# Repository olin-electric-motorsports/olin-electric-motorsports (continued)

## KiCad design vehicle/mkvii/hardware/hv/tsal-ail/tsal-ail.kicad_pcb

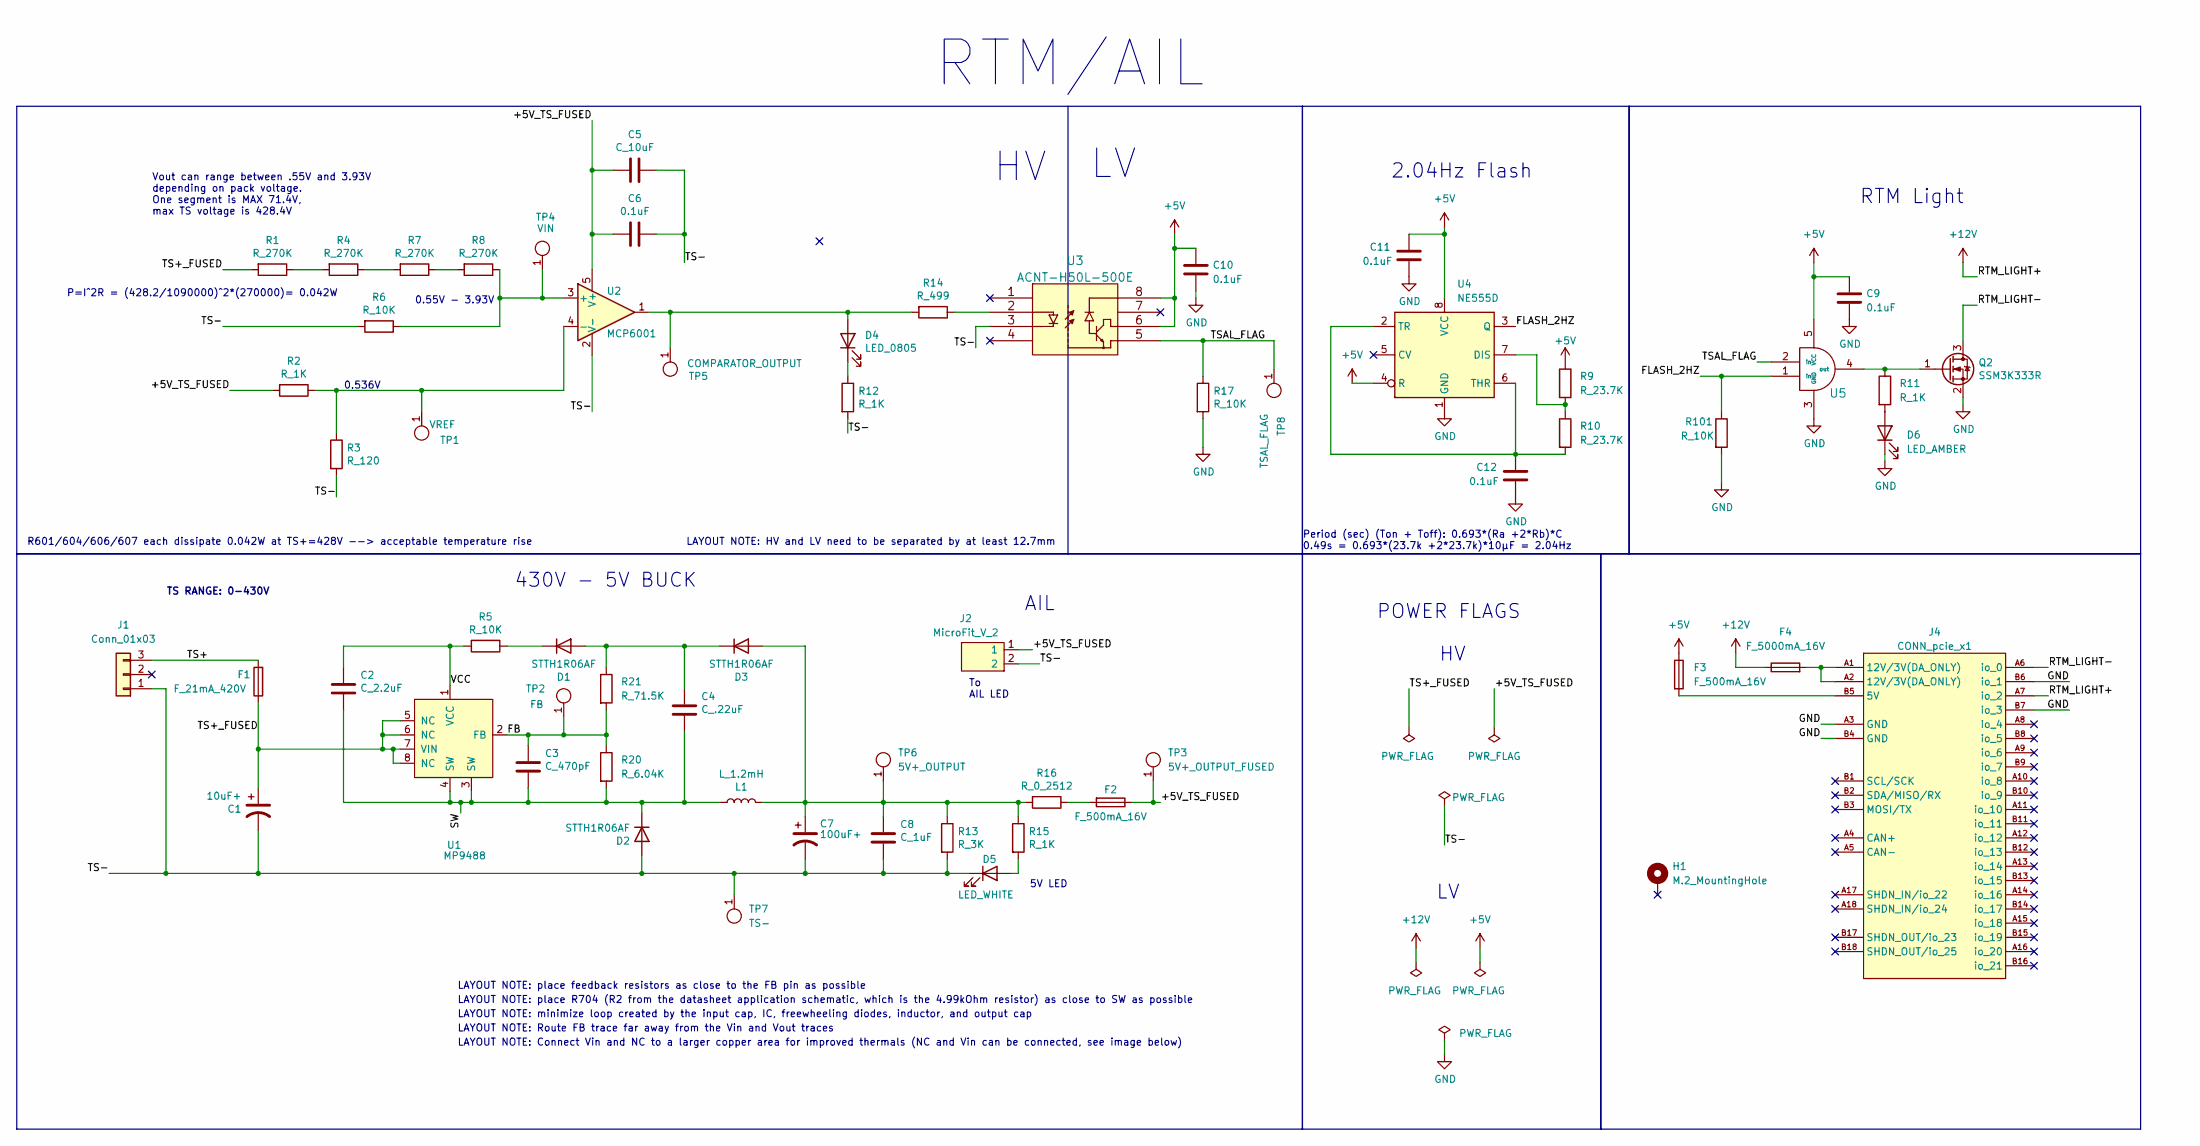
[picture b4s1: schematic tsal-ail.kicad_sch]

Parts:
C1: 10uF+; CP_Radial_D10.0mm_P5.00mm; MPN 450BXC10MEFC10X20
C2: C_2.2uF; C_0603; MPN GRM188R61E225KA12J
C3: C_470pF; C_0603; MPN 0603B471K500CT
C4: C_.22uF; C_0603; MPN CL10A224KB8NNNC
C5: C_10uF; C_0603; MPN LMK107BBJ106KALT
C6, C9, C10, C11, C12: 0.1uF; C_0603; MPN CL10B104KB8NNWC
C7: 100uF+; CP_Radial_D8.0mm_P3.50mm; MPN ESK107M050AG3EA
C8: C_1uF; C_0603; MPN CL10B105KA8NNNC
D1, D2, D3: STTH1R06AF; D_SOD-128; MPN STTH1R06AF
D4: LED_0805; CHIPLED_0805; MPN LTST-C170KFKT
D5: LED_WHITE; CHIPLED_0805; MPN B1701TW--20P000314U1930
D6: LED_AMBER; CHIPLED_0805
F1: F_21mA_420V; MPN B59884C0120A054
F2, F3: F_500mA_16V; Fuse_1210; MPN 0ZCH0050FF2G
F4: F_5000mA_16V; Fuse_1210; MPN 0ZCH0050FF2G
H1: M.2_MountingHole; M.2_Mount
J1: Conn_01x03; Molex_Micro-Fit_3.0_43650-0315_1x03_P3.00mm_Vertical
J2: MicroFit_V_2; MPN 0430450212
J4: CONN_pcie_x1; pcie_x1
L1: L_1.2mH; MPN RCP1317NP-122L
Q2: SSM3K333R; SOT-23F; MPN SSM3K333R,LF
R1, R4, R7, R8: R_270K; R_0603; MPN RMCF0603FT270K
R2, R11, R12, R15: R_1K; R_0603; MPN RMCF0603FT1K00
R3: R_120; R_0603; MPN RC0603FR-13120RL
R5, R6, R17, R101: R_10K; R_0603; MPN RMCF0603FT10K0
R9, R10: R_23.7K; R_0603; MPN RMCF0603FT22K0
R13: R_3K; R_0603; MPN RC0603FR-103KL
R14: R_499; R_0603; MPN RC0603FR-10499RL
R16: R_0_2512; R_2512_6332Metric; MPN CR2512-J/-000ELF
R20: R_6.04K; R_0603; MPN RMCF0603FT6K04
R21: R_71.5K; R_0603; MPN RMCF0603FT71K5
TP1: VREF; Test_Point_SMD; MPN 5019
TP2: FB; Test_Point_SMD; MPN 5019
TP3: 5V+_OUTPUT_FUSED; Test_Point_SMD; MPN 5019
TP4: VIN; Test_Point_SMD; MPN 5019
TP5: COMPARATOR_OUTPUT; Test_Point_SMD; MPN 5019
TP6: 5V+_OUTPUT; Test_Point_SMD; MPN 5019
TP7: TS-; Test_Point_SMD; MPN 5019
TP8: TSAL_FLAG; Test_Point_SMD; MPN 5019
U1: MP9488; Converter_DCDC_MPS_MP9488; MPN MP9488GS-Z
U2: MCP6001; SOT-353_SC-70-5; MPN MCP6001T-I/OT
U3: ACNT-H50L-500E; MPN ACNT-H50L-000E
U4: NE555D; SOIC-8_3.9x4.9mm_P1.27mm
U5: U_GATE_SN74LVC1G08DBVR; SOT-23-5_OEM; MPN SN74LVC1G08DBVR

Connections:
+5V: C9.1, C10.1, C11.2, F3.1, R9.1, U3.6, U3.8, U4.4 (R), U4.8 (VCC), U5.5 (VCC)
+12V: F4.1, J4.A7 (io_2)
/+5V_TS_FUSED: C5.2, C6.2, F2.1, J2.1, R2.2, TP3.1, U2.5 (V+)
/FB: C3.1, R20.1, R21.2, TP2.1, U1.2 (FB)
/FLASH_2HZ: R101.1, U4.3 (Q), U5.1 (in)
/RTM_LIGHT-: J4.A6 (io_0), Q2.3 (D)
/SW: C2.2, C3.2, C4.2, D2.1 (K), L1.1, R20.2, U1.3 (SW), U1.4 (SW)
/TS+: F1.2, J1.3
/TS+_FUSED: C1.1, F1.1, R1.2, U1.5 (NC), U1.6 (NC), U1.7 (VIN), U1.8 (NC)
/TS-: C1.2, C5.1, C6.1, C7.2, C8.2, D2.2 (A), D5.1 (K), J1.1, J2.2, R3.2, R6.2, R12.2, R13.2, TP7.1, U2.2 (V-), U3.3
/TSAL_FLAG: R17.1, TP8.1, U3.5, U5.2 (in)
/VCC: C2.1, R5.2, U1.1 (VCC)
GND: C9.2, C10.2, C11.1, C12.1, D6.1 (K), J4.A3 (GND), J4.B4 (GND), J4.B6 (io_1), J4.B7 (io_3), Q2.2 (S), R17.2, R101.2, U4.1 (GND), U5.3 (GND)
unnamed: C4.1, D1.2 (A), D3.1 (K), R21.1
unnamed: D1.1 (K), R5.1
unnamed: C7.1, C8.1, D3.2 (A), L1.2, R13.1, R15.1, R16.2, TP6.1
unnamed: D4.2 (A), R14.2, TP5.1, U2.1
unnamed: D4.1 (K), R12.1
unnamed: D5.2 (A), R15.2
unnamed: D6.2 (A), R11.2
unnamed: F2.2, R16.1
unnamed: F4.2, J4.A1 (12V/3V(DA_ONLY)), J4.A2 (12V/3V(DA_ONLY))
unnamed: F3.2, J4.B5 (5V)
unnamed: Q2.1 (G), R11.1, U5.4 (out)
unnamed: R1.1, R4.2
unnamed: R4.1, R7.2
unnamed: R7.1, R8.2
unnamed: R14.1, U3.2
unnamed: R6.1, R8.1, TP4.1, U2.3 (+)
unnamed: R2.1, R3.1, TP1.1, U2.4 (-)
unnamed: R9.2, R10.1, U4.7 (DIS)
unnamed: C12.2, R10.2, U4.2 (TR), U4.6 (THR)

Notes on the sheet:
LAYOUT NOTE: Route FB trace far away from the Vin and Vout traces
Period (sec) (Ton + Toff): 0.693*(Ra +2*Rb)*C 0.49s = 0.693*(23.7k +2*23.7k)*10µF = 2.04Hz
AIL
LAYOUT NOTE: minimize loop created by the input cap, IC, freewheeling diodes, inductor, and output cap
RTM Light
LAYOUT NOTE: Connect Vin and NC to a larger copper area for improved thermals (NC and Vin can be connected, see image below)
RTM/AIL
2.04Hz Flash
P=I^2R = (428.2/1090000)^2*(270000)= 0.042W
LAYOUT NOTE: place feedback resistors as close to the FB pin as possible
Vout can range between .55V and 3.93V depending on pack voltage. One segment is MAX 71.4V, max TS voltage is 428.4V
LAYOUT NOTE: place R704 (R2 from the datasheet application schematic, which is the 4.99kOhm resistor) as close to SW as possible
LAYOUT NOTE: HV and LV need to be separated by at least 12.7mm
5V LED
POWER FLAGS
0.536V
R601/604/606/607 each dissipate 0.042W at TS+=428V --> acceptable temperature rise
0.55V - 3.93V
TS RANGE: 0-430V
To AIL LED
430V - 5V BUCK

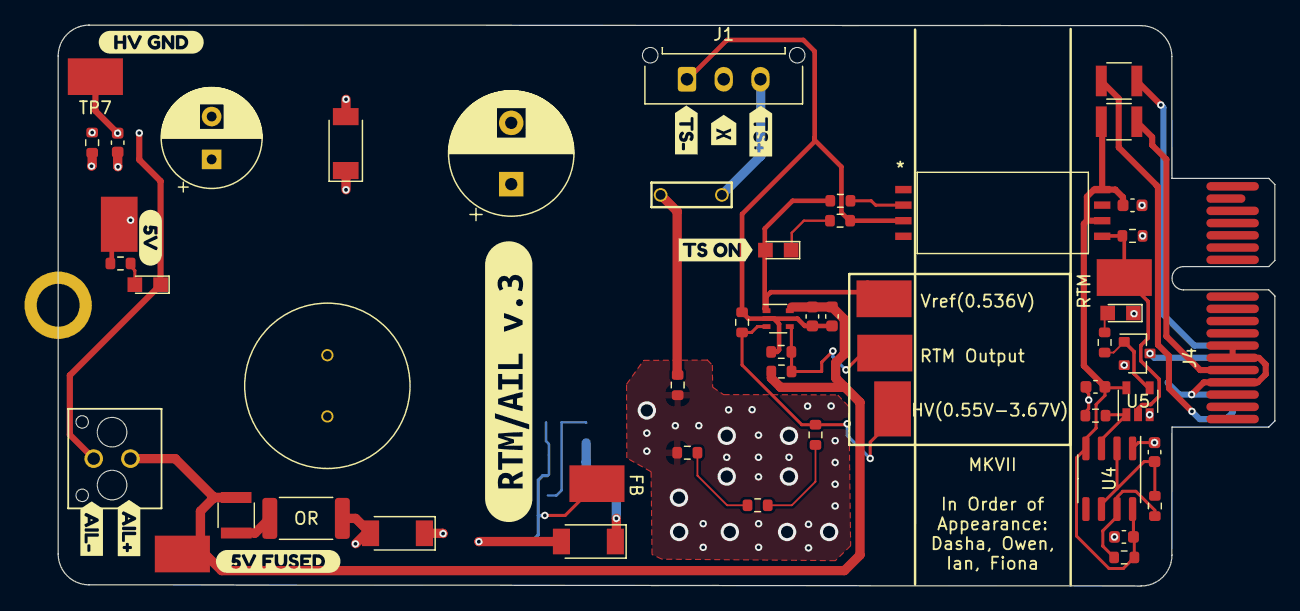
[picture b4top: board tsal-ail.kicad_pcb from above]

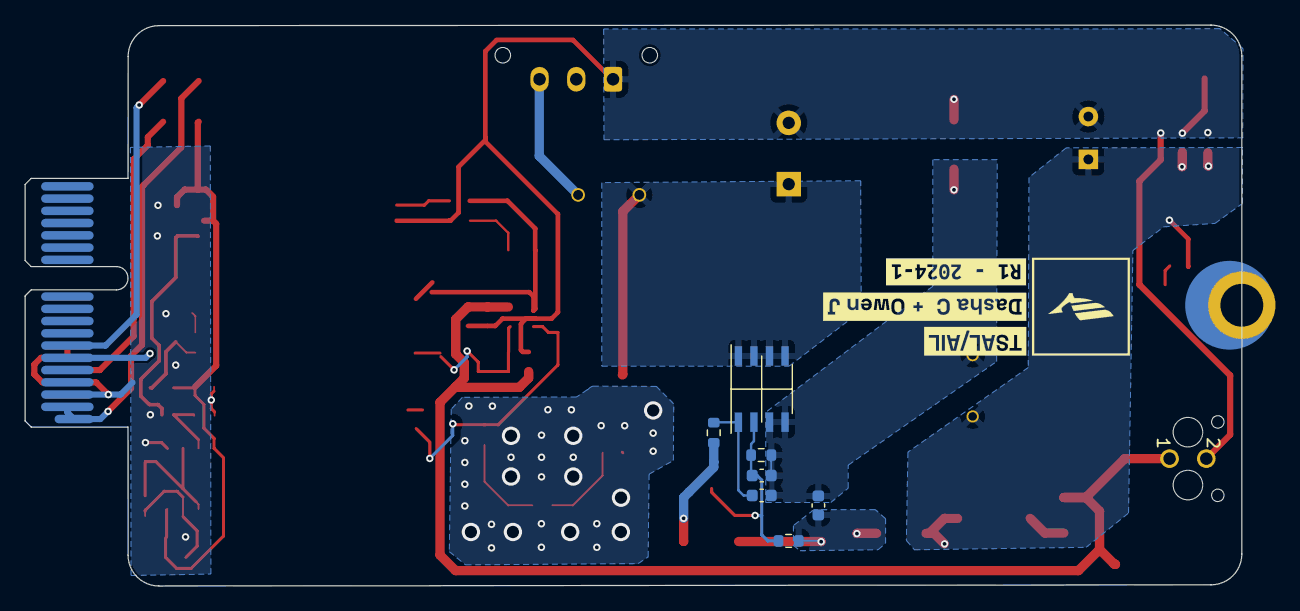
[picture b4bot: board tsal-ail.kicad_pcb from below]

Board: 2 copper layers, 99.3 x 45.8 mm, 74 parts (10 on the bottom side), 32 nets.

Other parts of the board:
kibuzzard-63AC91FD: G***; kibuzzard-63AC91FD
kibuzzard-63AC93EB: G***; kibuzzard-63AC93EB
kibuzzard-63AC93FC: G***; kibuzzard-63AC93FC
kibuzzard-63AC9220: G***; kibuzzard-63AC9220
kibuzzard-63AC9283: G***; kibuzzard-63AC9283
kibuzzard-63AC9446: G***; kibuzzard-63AC9446
kibuzzard-63AC9456: G***; kibuzzard-63AC9456
kibuzzard-63AD0077: G***; kibuzzard-63AD0077
kibuzzard-63D843BA: G***; kibuzzard-63D843BA
kibuzzard-63D84460: G***; kibuzzard-63D84460
kibuzzard-673C33E6: G***; kibuzzard-673C33E6
kibuzzard-6784A725: G***; kibuzzard-6784A725
kibuzzard-6784B342: G***; kibuzzard-6784B342

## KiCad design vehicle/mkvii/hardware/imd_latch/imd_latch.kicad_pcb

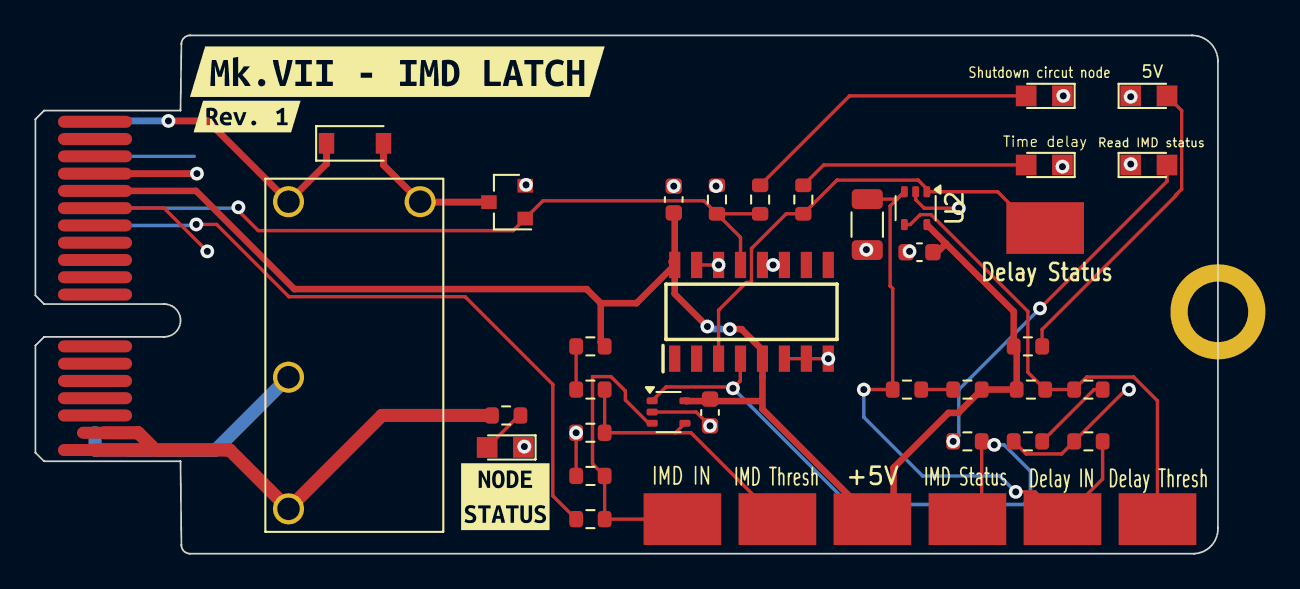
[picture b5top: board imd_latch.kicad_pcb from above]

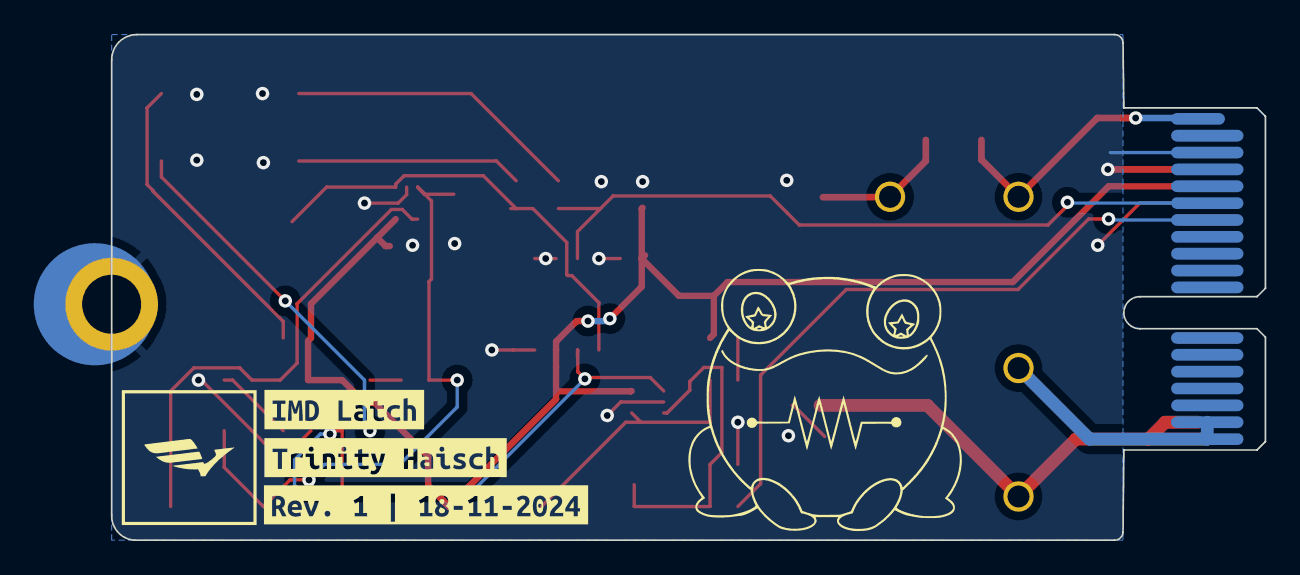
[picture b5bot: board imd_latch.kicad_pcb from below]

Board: 2 copper layers, 68.4 x 30.0 mm, 47 parts (3 on the bottom side), 22 nets.

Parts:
+5V: Test_Point_SMD
C1: C_22uF; C_1206_3216Metric
C2, C3, C4: 0.1uF; C_0603
D1: D_Schottky_SS110LW; D_SOD-123
D2, D4, D5: LED_AMBER; CHIPLED_0805
D3: LED_WHITE; CHIPLED_0805
D6: LED_BLUE; CHIPLED_0805
Delay IN: Test_Point_SMD
Delay Status: Test_Point_SMD
Delay Thresh: Test_Point_SMD
H1: M.2_MountingHole; M.2_Mount
IC1: CD4044BDR; SOIC127P600X175-16N
IMD IN: Test_Point_SMD
IMD Status: Test_Point_SMD
IMD Thresh: Test_Point_SMD
J2: CONN_pcie_x1; pcie_x1
K1: G5Q-1A4-DC12; Relay_SPST_OMRON-G5Q-1A4_OEM
Q1: SSM3K333R; SOT-23F
R1, R3, R4, R6, R7, R11: R_100K; R_0603
R2: R_71.5k; R_0603
R5: R_120K; R_0603
R8: R_3K; R_0603
R9, R13, R15, R16, R17: R_1K; R_0603
R10: R_1.82M; R_0603
R12: R_604K; R_0603
R14: R_330; R_0603
U1, U2: MCP6001; SOT-353_SC-70-5
kibuzzard-673ACD76: G***; kibuzzard-673ACD76
kibuzzard-673AD5BE: G***; kibuzzard-673AD5BE
kibuzzard-673AD5DE: G***; kibuzzard-673AD5DE
kibuzzard-673AD216: G***; kibuzzard-673AD216
kibuzzard-673AD632: G***; kibuzzard-673AD632
kibuzzard-673AE0C6: G***; kibuzzard-673AE0C6

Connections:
+5V: +5V.1, C2.1, C3.1, C4.1, IC1.5 (ENABLE), IC1.16 (VDD), J2.B5 (5V), R1.1, R2.2, R3.1, R14.2, U1.5 (V+), U2.5 (V+)
+BATT: D1.1 (K), J2.A1 (12V/3V(DA_ONLY)), K1.1
/IMD_OUTPUT: J2.A7 (io_2), R8.1
/IMD_STATUS: IC1.13 (Q1), J2.A6 (io_0), Q1.1 (G), R12.1, R13.1
/IMD_STATUS_OUTPUT: IC1.4 (RI), IMD Status.1, R15.1, U1.1
/SHDN_IN: J2.A17 (SHDN_IN/io_22), J2.A18 (SHDN_IN/io_24), K1.2
/SHDN_OUT: J2.B17 (SHDN_OUT/io_23), J2.B18 (SHDN_OUT/io_25), K1.3, R17.1
/TIME_DELAY: Delay Status.1, IC1.3 (SI), R16.1, U2.1
GND: C1.2, C2.2, C3.2, C4.2, D2.1 (K), D3.1 (K), D4.1 (K), D5.1 (K), D6.1 (K), H1.1, IC1.6 (R2), IC1.7 (S2), IC1.8 (VSS), IC1.11 (S3), IC1.12 (R3), IC1.14 (R4), IC1.15 (S4), J2.A3 (GND), J2.B4 (GND), J2.B6 (io_1), Q1.2 (S), R6.1, R7.1, R9.2, R10.2, R12.2, U1.2 (V-), U2.2 (V-)
unnamed: D1.2 (A), K1.5, Q1.3 (D)
unnamed: D2.2 (A), R15.2
unnamed: D3.2 (A), R14.1
unnamed: D4.2 (A), R13.2
unnamed: D5.2 (A), R16.2
unnamed: D6.2 (A), R17.2
unnamed: R2.1, R5.1
unnamed: R4.1, R7.2
unnamed: R3.2, R11.1
unnamed: IMD IN.1, R8.2, R9.1, U1.3 (+)
unnamed: IMD Thresh.1, R6.2, R11.2, U1.4 (-)
unnamed: C1.1, Delay IN.1, R5.2, R10.1, U2.3 (+)
unnamed: Delay Thresh.1, R1.2, R4.2, U2.4 (-)

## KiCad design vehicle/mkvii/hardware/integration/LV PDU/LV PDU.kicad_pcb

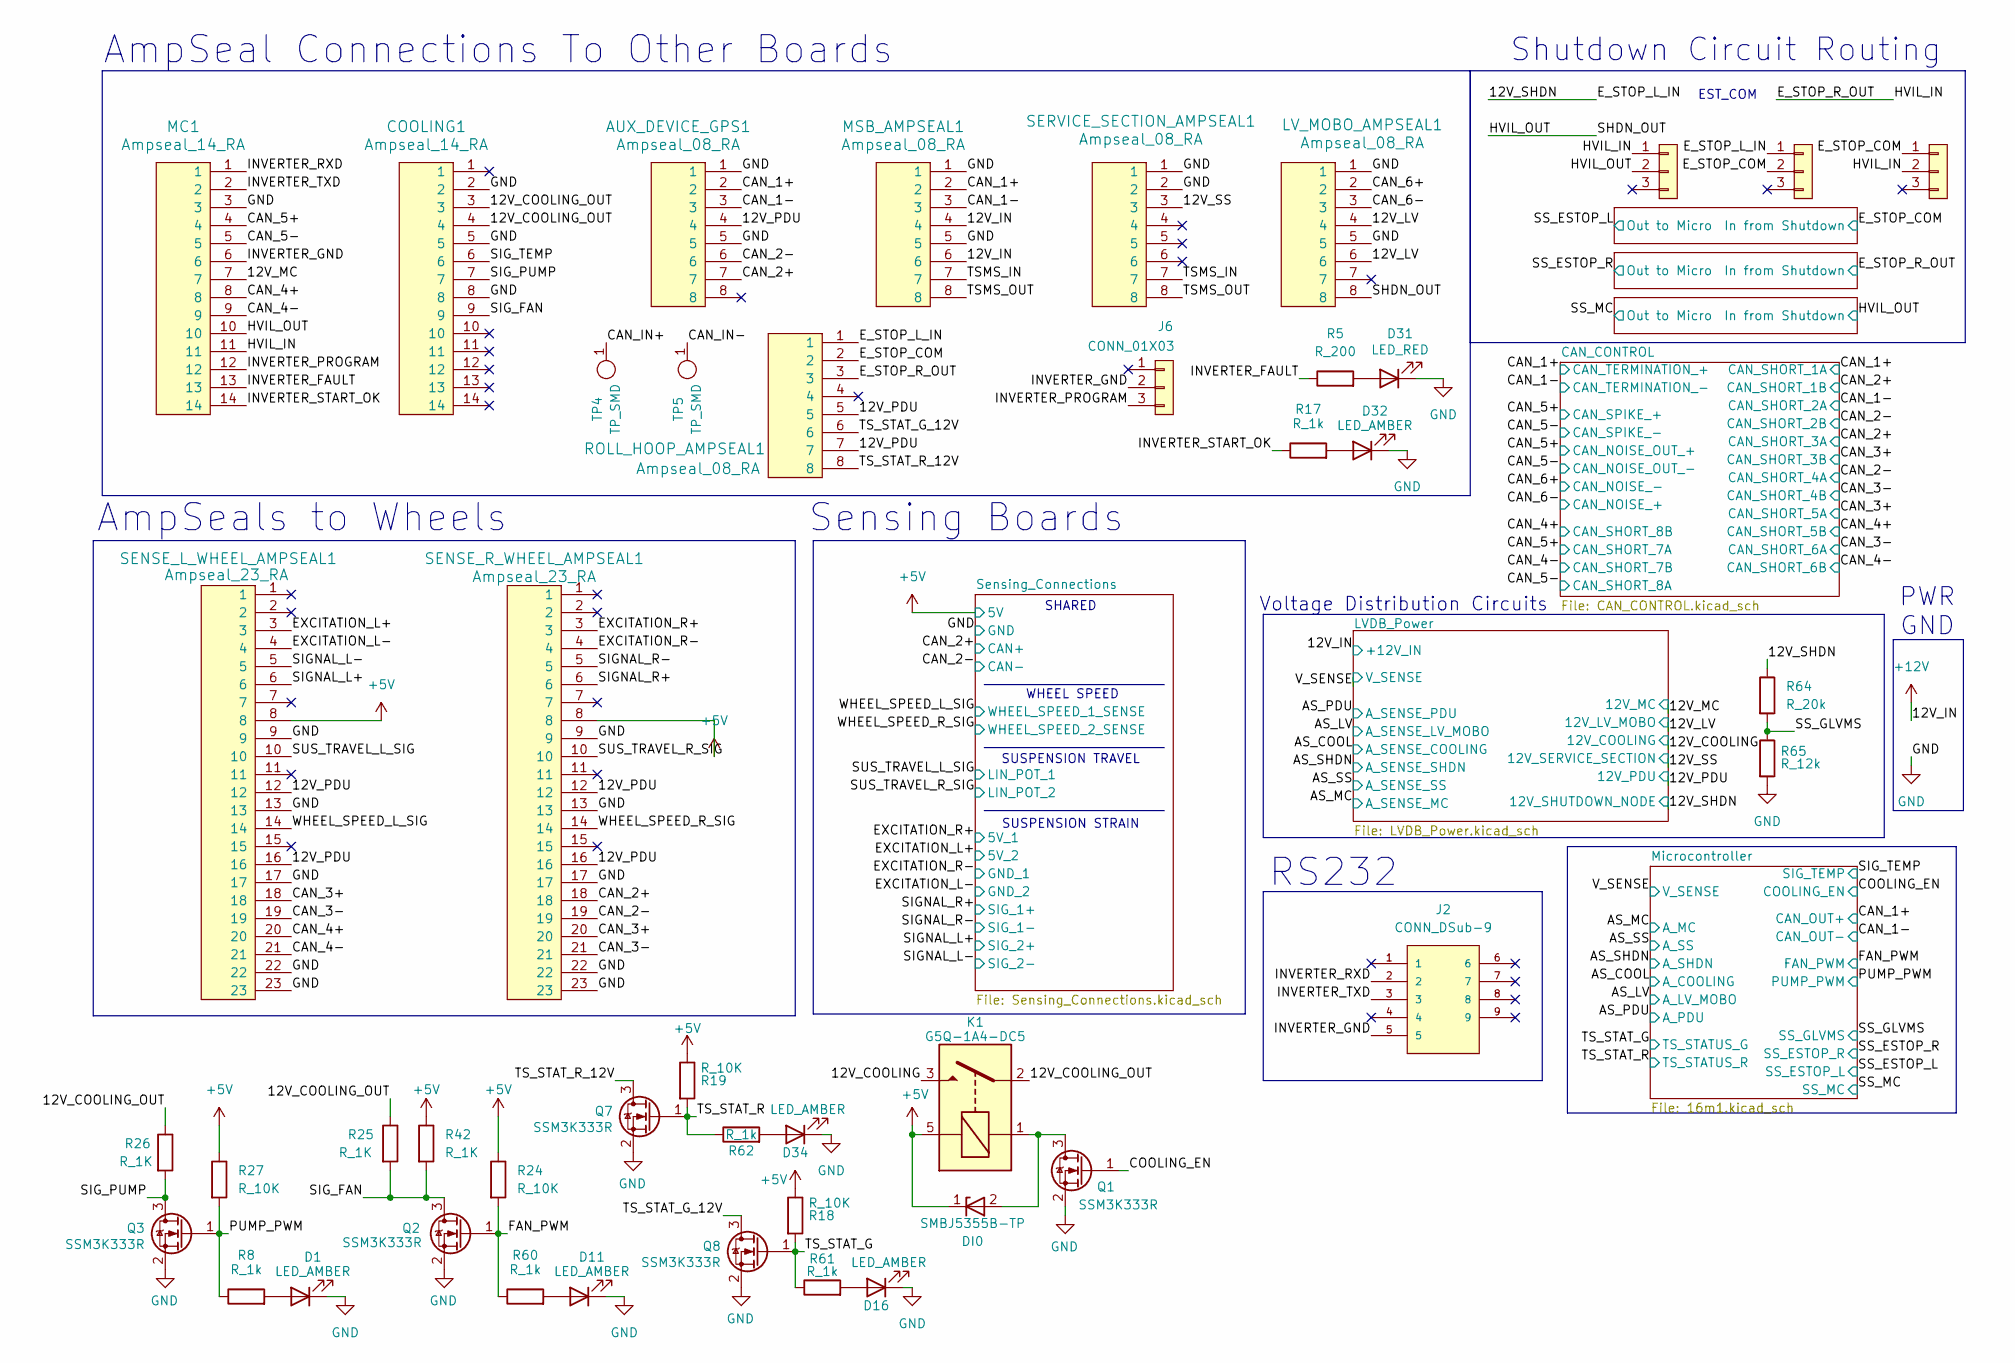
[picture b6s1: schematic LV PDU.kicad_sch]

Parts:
AUX_DEVICE_GPS1: Ampseal_08_RA; Ampseal_8_RA; MPN 1-776279-1
COOLING1: Ampseal_14_RA; MPN 1-776266-1
D1, D11, D16, D32, D34: LED_AMBER; CHIPLED_0805
D31: LED_RED; CHIPLED_0805
DI0: SMBJ5355B-TP; DO-214AA; MPN SMBJ5355B-TP
J2: CONN_DSub-9; TE_5745781-4; MPN 5745781-4
J6, J12, J13, J14: CONN_01X03; PinHeader_1x03_P2.54mm_Vertical; MPN PH1-03-UA
K1: G5Q-1A4-DC5; Relay_SPST_OMRON-G5Q-1A4_OEM; MPN G5Q-1A4 DC5
LV_MOBO_AMPSEAL1: Ampseal_08_RA; Ampseal_8_RA; MPN 1-776279-1
MC1: Ampseal_14_RA; MPN 1-776266-1
MSB_AMPSEAL1: Ampseal_08_RA; Ampseal_8_RA; MPN 1-776279-1
Q1, Q2, Q3, Q7, Q8: SSM3K333R; SOT-23F; MPN SSM3K333R,LF
R5: R_200; R_0603; MPN RC0603FR-13200RL
R8, R17, R60, R61, R62: R_1k; R_0603; MPN RC0603FR-13200RL
R18, R19, R24, R27: R_10K; R_0603; MPN RC0603FR-13200RL
R25, R26, R42: R_1K; R_0603; MPN RC0603FR-13200RL
R64: R_20k; R_0603; MPN RC0603FR-13200RL
R65: R_12k; R_0603; MPN RC0603FR-13200RL
ROLL_HOOP_AMPSEAL1: Ampseal_08_RA; Ampseal_8_RA; MPN 1-776279-1
SENSE_L_WHEEL_AMPSEAL1: Ampseal_23_RA; MPN 776087-1
SENSE_R_WHEEL_AMPSEAL1: Ampseal_23_RA; MPN 776087-1
SERVICE_SECTION_AMPSEAL1: Ampseal_08_RA; Ampseal_8_RA; MPN 1-776279-1
TP4, TP5: TP_SMD; Test_Point_SMD; MPN 5019

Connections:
+5V: DI0.1 (K), K1.5, R18.1, R19.1, R24.1, R27.1, R42.1, SENSE_L_WHEEL_AMPSEAL1.8, SENSE_R_WHEEL_AMPSEAL1.8; also elsewhere on the board
+12V: MSB_AMPSEAL1.4, MSB_AMPSEAL1.6; also elsewhere on the board
/12V_COOLING: K1.3; also elsewhere on the board
/12V_COOLING_OUT: COOLING1.3, COOLING1.4, K1.2, R25.1, R26.1
/12V_LV: LV_MOBO_AMPSEAL1.4, LV_MOBO_AMPSEAL1.6; also elsewhere on the board
/12V_MC: MC1.7; also elsewhere on the board
/12V_PDU: AUX_DEVICE_GPS1.4, ROLL_HOOP_AMPSEAL1.5, ROLL_HOOP_AMPSEAL1.7, SENSE_L_WHEEL_AMPSEAL1.12, SENSE_L_WHEEL_AMPSEAL1.16, SENSE_R_WHEEL_AMPSEAL1.12, SENSE_R_WHEEL_AMPSEAL1.16; also elsewhere on the board
/12V_SHDN: J12.1, R64.1, ROLL_HOOP_AMPSEAL1.1; also elsewhere on the board
/12V_SS: SERVICE_SECTION_AMPSEAL1.3; also elsewhere on the board
/CAN_1+: AUX_DEVICE_GPS1.2, MSB_AMPSEAL1.2; also elsewhere on the board
/CAN_1-: AUX_DEVICE_GPS1.3, MSB_AMPSEAL1.3; also elsewhere on the board
/CAN_2+: AUX_DEVICE_GPS1.7, SENSE_R_WHEEL_AMPSEAL1.18; also elsewhere on the board
/CAN_2-: AUX_DEVICE_GPS1.6, SENSE_R_WHEEL_AMPSEAL1.19; also elsewhere on the board
/CAN_3+: SENSE_L_WHEEL_AMPSEAL1.18, SENSE_R_WHEEL_AMPSEAL1.20; also elsewhere on the board
/CAN_3-: SENSE_L_WHEEL_AMPSEAL1.19, SENSE_R_WHEEL_AMPSEAL1.21; also elsewhere on the board
/CAN_4+: MC1.8, SENSE_L_WHEEL_AMPSEAL1.20; also elsewhere on the board
/CAN_4-: MC1.9, SENSE_L_WHEEL_AMPSEAL1.21; also elsewhere on the board
/CAN_5+: MC1.4; also elsewhere on the board
/CAN_5-: MC1.5; also elsewhere on the board
/CAN_6+: LV_MOBO_AMPSEAL1.2; also elsewhere on the board
/CAN_6-: LV_MOBO_AMPSEAL1.3; also elsewhere on the board
/CAN_IN+: TP4.1
/CAN_IN-: TP5.1
/COOLING_EN: Q1.1 (G); also elsewhere on the board
/EXCITATION_L+: SENSE_L_WHEEL_AMPSEAL1.3; also elsewhere on the board
/EXCITATION_L-: SENSE_L_WHEEL_AMPSEAL1.4; also elsewhere on the board
/EXCITATION_R+: SENSE_R_WHEEL_AMPSEAL1.3; also elsewhere on the board
/EXCITATION_R-: SENSE_R_WHEEL_AMPSEAL1.4; also elsewhere on the board
/E_STOP_COM: J12.2, J13.1, ROLL_HOOP_AMPSEAL1.2; also elsewhere on the board
/E_STOP_R_OUT: J13.2, J14.1, MC1.11, ROLL_HOOP_AMPSEAL1.3; also elsewhere on the board
/FAN_PWM: Q2.1 (G), R24.2, R60.1; also elsewhere on the board
/HVIL_OUT: J14.2, LV_MOBO_AMPSEAL1.8, MC1.10; also elsewhere on the board
/INVERTER_FAULT: MC1.13, R5.1
/INVERTER_GND: J2.5, J6.2, MC1.6
/INVERTER_PROGRAM: J6.3, MC1.12
/INVERTER_RXD: J2.2, MC1.1
/INVERTER_START_OK: MC1.14, R17.1
/INVERTER_TXD: J2.3, MC1.2
/PUMP_PWM: Q3.1 (G), R8.1, R27.2; also elsewhere on the board
/SIGNAL_L+: SENSE_L_WHEEL_AMPSEAL1.6; also elsewhere on the board
/SIGNAL_L-: SENSE_L_WHEEL_AMPSEAL1.5; also elsewhere on the board
/SIGNAL_R+: SENSE_R_WHEEL_AMPSEAL1.6; also elsewhere on the board
/SIGNAL_R-: SENSE_R_WHEEL_AMPSEAL1.5; also elsewhere on the board
/SIG_FAN: COOLING1.9, Q2.3 (D), R25.2, R42.2
/SIG_PUMP: COOLING1.7, Q3.3 (D), R26.2
/SIG_TEMP: COOLING1.6; also elsewhere on the board
/SS_GLVMS: R64.2, R65.1; also elsewhere on the board
/SUS_TRAVEL_L_SIG: SENSE_L_WHEEL_AMPSEAL1.10; also elsewhere on the board
/SUS_TRAVEL_R_SIG: SENSE_R_WHEEL_AMPSEAL1.10; also elsewhere on the board
/TSMS_IN: MSB_AMPSEAL1.7, SERVICE_SECTION_AMPSEAL1.7
/TSMS_OUT: MSB_AMPSEAL1.8, SERVICE_SECTION_AMPSEAL1.8
/TS_STAT_G: Q8.1 (G), R18.2, R61.1; also elsewhere on the board
/TS_STAT_G_12V: Q8.3 (D), ROLL_HOOP_AMPSEAL1.6
/TS_STAT_R: Q7.1 (G), R19.2, R62.1; also elsewhere on the board
/TS_STAT_R_12V: Q7.3 (D), ROLL_HOOP_AMPSEAL1.8
/WHEEL_SPEED_L_SIG: SENSE_L_WHEEL_AMPSEAL1.14; also elsewhere on the board
/WHEEL_SPEED_R_SIG: SENSE_R_WHEEL_AMPSEAL1.14; also elsewhere on the board
GND: AUX_DEVICE_GPS1.1, AUX_DEVICE_GPS1.5, COOLING1.2, COOLING1.5, COOLING1.8, D1.1 (K), D11.1 (K), D16.1 (K), D31.1 (K), D32.1 (K), D34.1 (K), LV_MOBO_AMPSEAL1.1, LV_MOBO_AMPSEAL1.5, MC1.3, MSB_AMPSEAL1.1, MSB_AMPSEAL1.5, Q1.2 (S), Q2.2 (S), Q3.2 (S), Q7.2 (S), Q8.2 (S), R65.2, SENSE_L_WHEEL_AMPSEAL1.9, SENSE_L_WHEEL_AMPSEAL1.13, SENSE_L_WHEEL_AMPSEAL1.17, SENSE_L_WHEEL_AMPSEAL1.22, SENSE_L_WHEEL_AMPSEAL1.23, SENSE_R_WHEEL_AMPSEAL1.9, SENSE_R_WHEEL_AMPSEAL1.13, SENSE_R_WHEEL_AMPSEAL1.17, SENSE_R_WHEEL_AMPSEAL1.22, SENSE_R_WHEEL_AMPSEAL1.23, SERVICE_SECTION_AMPSEAL1.1, SERVICE_SECTION_AMPSEAL1.2; also elsewhere on the board
unnamed: D1.2 (A), R8.2
unnamed: D11.2 (A), R60.2
unnamed: D16.2 (A), R61.2
unnamed: D31.2 (A), R5.2
unnamed: D32.2 (A), R17.2
unnamed: D34.2 (A), R62.2
unnamed: DI0.2 (A), K1.1, Q1.3 (D)

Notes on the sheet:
AmpSeal Connections To Other Boards
RS232
WHEEL SPEED
EST_COM
Shutdown Circuit Routing
SUSPENSION TRAVEL
AmpSeals to Wheels
Voltage Distribution Circuits
SHARED
SUSPENSION STRAIN
PWR GND
Sensing Boards

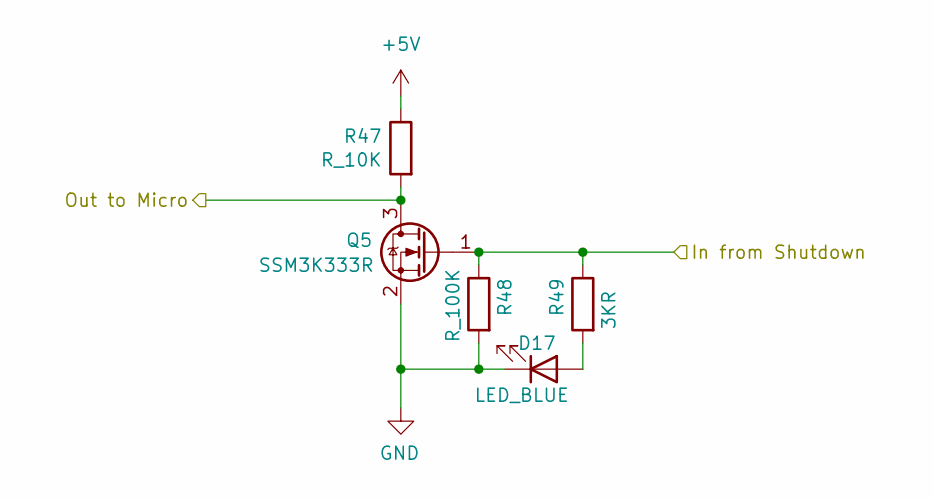
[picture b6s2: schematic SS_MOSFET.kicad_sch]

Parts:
D17: LED_BLUE; CHIPLED_0805; MPN LTST-C171TBKT
Q5: SSM3K333R; SOT-23F; MPN SSM3K333R,LF
R47: R_10K; R_0603; MPN RMCF0603FT10K0
R48: R_100K; R_0603; MPN RMCF0603FT100K
R49: 3KR; R_0603; MPN RC0603FR-103KL

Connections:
+5V: R47.1; also elsewhere on the board
/E_STOP_R_OUT: Q5.1 (G), R48.1, R49.1; also elsewhere on the board
/SS_ESTOP_R: Q5.3 (D), R47.2; also elsewhere on the board
GND: D17.1 (K), Q5.2 (S), R48.2; also elsewhere on the board
unnamed: D17.2 (A), R49.2

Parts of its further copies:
D6, D33: LED_BLUE; CHIPLED_0805; MPN LTST-C171TBKT
Q4, Q6: SSM3K333R; SOT-23F; MPN SSM3K333R,LF
R7, R50: R_10K; R_0603; MPN RMCF0603FT10K0
R15, R51: R_100K; R_0603; MPN RMCF0603FT100K
R16, R52: 3KR; R_0603; MPN RC0603FR-103KL

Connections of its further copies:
+5V: R7.1, R50.1; also elsewhere on the board
/E_STOP_COM: Q4.1 (G), R15.1, R16.1; also elsewhere on the board
/HVIL_OUT: Q6.1 (G), R51.1, R52.1; also elsewhere on the board
/SS_ESTOP_L: Q4.3 (D), R7.2; also elsewhere on the board
/SS_MC: Q6.3 (D), R50.2; also elsewhere on the board
GND: D6.1 (K), D33.1 (K), Q4.2 (S), Q6.2 (S), R15.2, R51.2; also elsewhere on the board
unnamed: D6.2 (A), R16.2
unnamed: D33.2 (A), R52.2

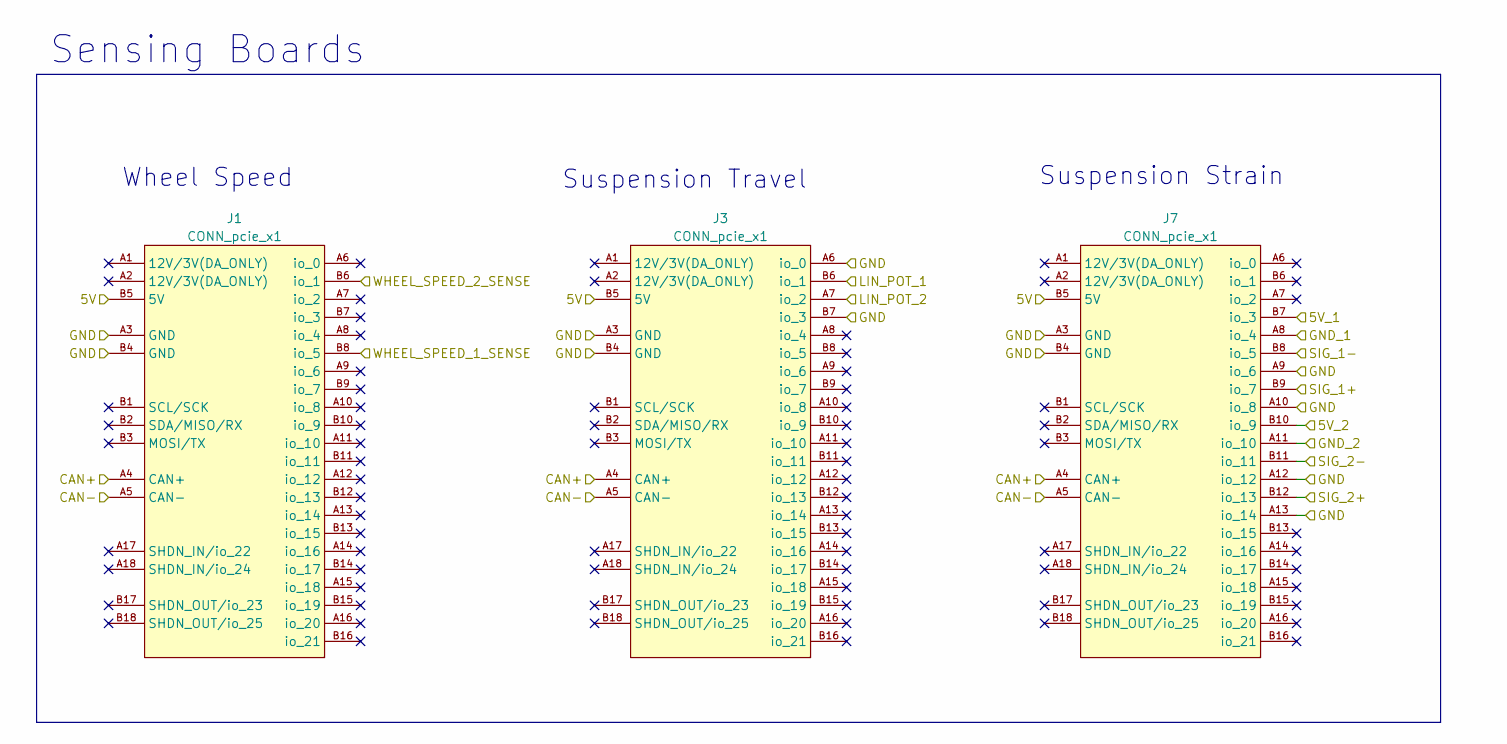
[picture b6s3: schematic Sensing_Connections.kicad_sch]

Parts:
J1, J3, J7: CONN_pcie_x1; te_pcie_x1_connector

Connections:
+5V: J1.B5 (5V), J3.B5 (5V), J7.B5 (5V); also elsewhere on the board
/CAN_2+: J1.A4 (CAN+), J3.A4 (CAN+), J7.A4 (CAN+); also elsewhere on the board
/CAN_2-: J1.A5 (CAN-), J3.A5 (CAN-), J7.A5 (CAN-); also elsewhere on the board
/EXCITATION_L+: J7.B10 (io_9); also elsewhere on the board
/EXCITATION_L-: J7.A11 (io_10); also elsewhere on the board
/EXCITATION_R+: J7.B7 (io_3); also elsewhere on the board
/EXCITATION_R-: J7.A8 (io_4); also elsewhere on the board
/SIGNAL_L+: J7.B12 (io_13); also elsewhere on the board
/SIGNAL_L-: J7.B11 (io_11); also elsewhere on the board
/SIGNAL_R+: J7.B9 (io_7); also elsewhere on the board
/SIGNAL_R-: J7.B8 (io_5); also elsewhere on the board
/SUS_TRAVEL_L_SIG: J3.B6 (io_1); also elsewhere on the board
/SUS_TRAVEL_R_SIG: J3.A7 (io_2); also elsewhere on the board
/WHEEL_SPEED_L_SIG: J1.B8 (io_5); also elsewhere on the board
/WHEEL_SPEED_R_SIG: J1.B6 (io_1); also elsewhere on the board
GND: J1.A3 (GND), J1.B4 (GND), J3.A3 (GND), J3.A6 (io_0), J3.B4 (GND), J3.B7 (io_3), J7.A3 (GND), J7.A9 (io_6), J7.A10 (io_8), J7.A12 (io_12), J7.A13 (io_14), J7.B4 (GND); also elsewhere on the board

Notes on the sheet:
Sensing Boards
Suspension Travel
Wheel Speed
Suspension Strain

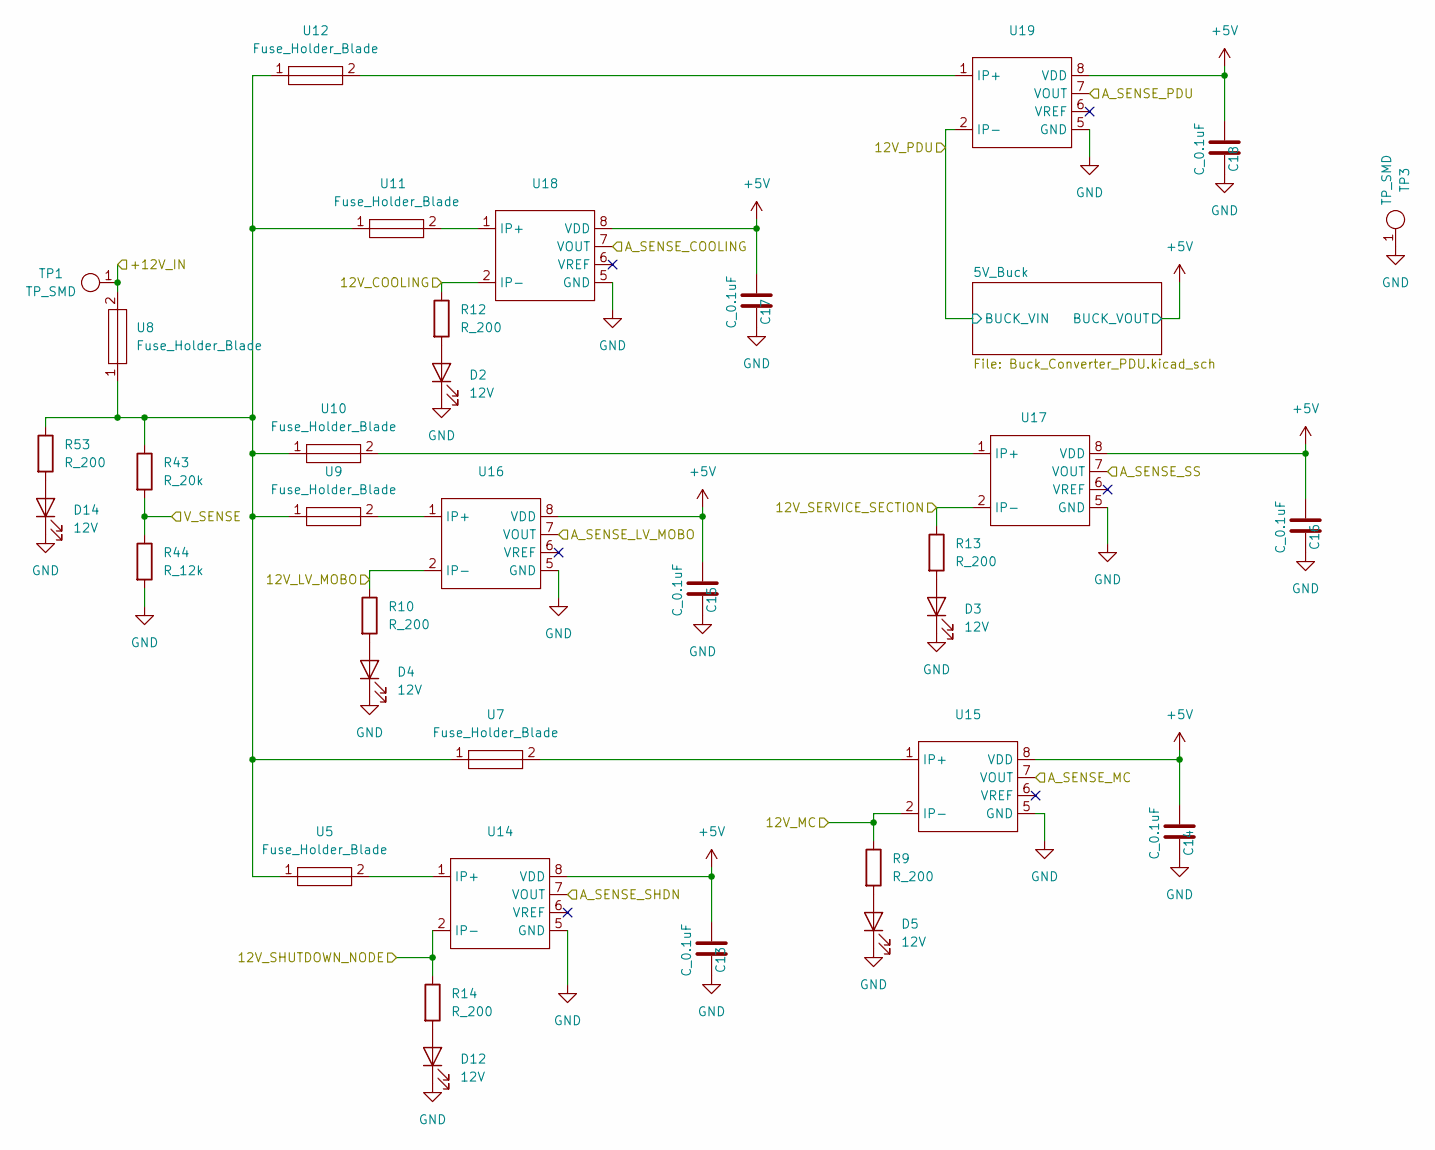
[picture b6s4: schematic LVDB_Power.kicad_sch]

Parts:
C13, C14, C15, C16, C17, C18: C_0.1uF; C_0603_1608Metric; MPN 478-3352-1-ND
D2, D3, D4, D5, D12, D14: 12V; CHIPLED_0805; MPN 475-1410-1-ND
R9, R10, R12, R13, R14, R53: R_200; R_0603; MPN RC0603FR-13200RL
R43: R_20k; R_0603; MPN RC0603FR-13200RL
R44: R_12k; R_0603; MPN RC0603FR-13200RL
TP1, TP3: TP_SMD; Test_Point_SMD; MPN 5019
U5, U7, U8, U9, U10, U11, U12: Fuse_Holder_Blade; Fuse_Block_Holder
U14, U15, U16, U17, U18, U19: ACS37010

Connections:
+5V: C13.1, C14.1, C15.1, C16.1, C17.1, C18.1, U14.8 (VDD), U15.8 (VDD), U16.8 (VDD), U17.8 (VDD), U18.8 (VDD), U19.8 (VDD); also elsewhere on the board
+12V: TP1.1, U8.2; also elsewhere on the board
/12V_COOLING: R12.1, U18.2 (IP-); also elsewhere on the board
/12V_LV: R10.1, U16.2 (IP-); also elsewhere on the board
/12V_MC: R9.1, U15.2 (IP-); also elsewhere on the board
/12V_PDU: U19.2 (IP-); also elsewhere on the board
/12V_SHDN: R14.1, U14.2 (IP-); also elsewhere on the board
/12V_SS: R13.1, U17.2 (IP-); also elsewhere on the board
/AS_COOL: U18.7 (VOUT); also elsewhere on the board
/AS_LV: U16.7 (VOUT); also elsewhere on the board
/AS_MC: U15.7 (VOUT); also elsewhere on the board
/AS_PDU: U19.7 (VOUT); also elsewhere on the board
/AS_SHDN: U14.7 (VOUT); also elsewhere on the board
/AS_SS: U17.7 (VOUT); also elsewhere on the board
/V_SENSE: R43.2, R44.1; also elsewhere on the board
GND: C13.2, C14.2, C15.2, C16.2, C17.2, C18.2, D2.1 (K), D3.1 (K), D4.1 (K), D5.1 (K), D12.1 (K), D14.1 (K), R44.2, TP3.1, U14.5 (GND), U15.5 (GND), U16.5 (GND), U17.5 (GND), U18.5 (GND), U19.5 (GND); also elsewhere on the board
unnamed: D2.2 (A), R12.2
unnamed: D3.2 (A), R13.2
unnamed: D4.2 (A), R10.2
unnamed: D5.2 (A), R9.2
unnamed: D12.2 (A), R14.2
unnamed: D14.2 (A), R53.2
unnamed: R43.1, R53.1, U5.1, U7.1, U8.1, U9.1, U10.1, U11.1, U12.1
unnamed: U5.2, U14.1 (IP+)
unnamed: U7.2, U15.1 (IP+)
unnamed: U9.2, U16.1 (IP+)
unnamed: U10.2, U17.1 (IP+)
unnamed: U11.2, U18.1 (IP+)
unnamed: U12.2, U19.1 (IP+)
